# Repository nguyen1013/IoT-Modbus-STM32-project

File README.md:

# IoT-Modbus-STM32-project (this project is a work in progress)

## 1. Introduction
This project showcases a compact but realistic home‑automation system built with STM32 microcontrollers, Modbus RTU over RS‑485, and cloud integration via an IoT gateway. Each STM32 node gathers sensor data—temperature, humidity, light, CO₂, and AC voltage—and sends it to a PC gateway for processing and visualisation. The setup highlights practical embedded engineering: real‑time operation, safe hardware design, reliable communication, and a scalable architecture suitable for smart‑home or educational use.

<p align="center">
  <br>
  <b>The General Project Architecture</b>
</p>

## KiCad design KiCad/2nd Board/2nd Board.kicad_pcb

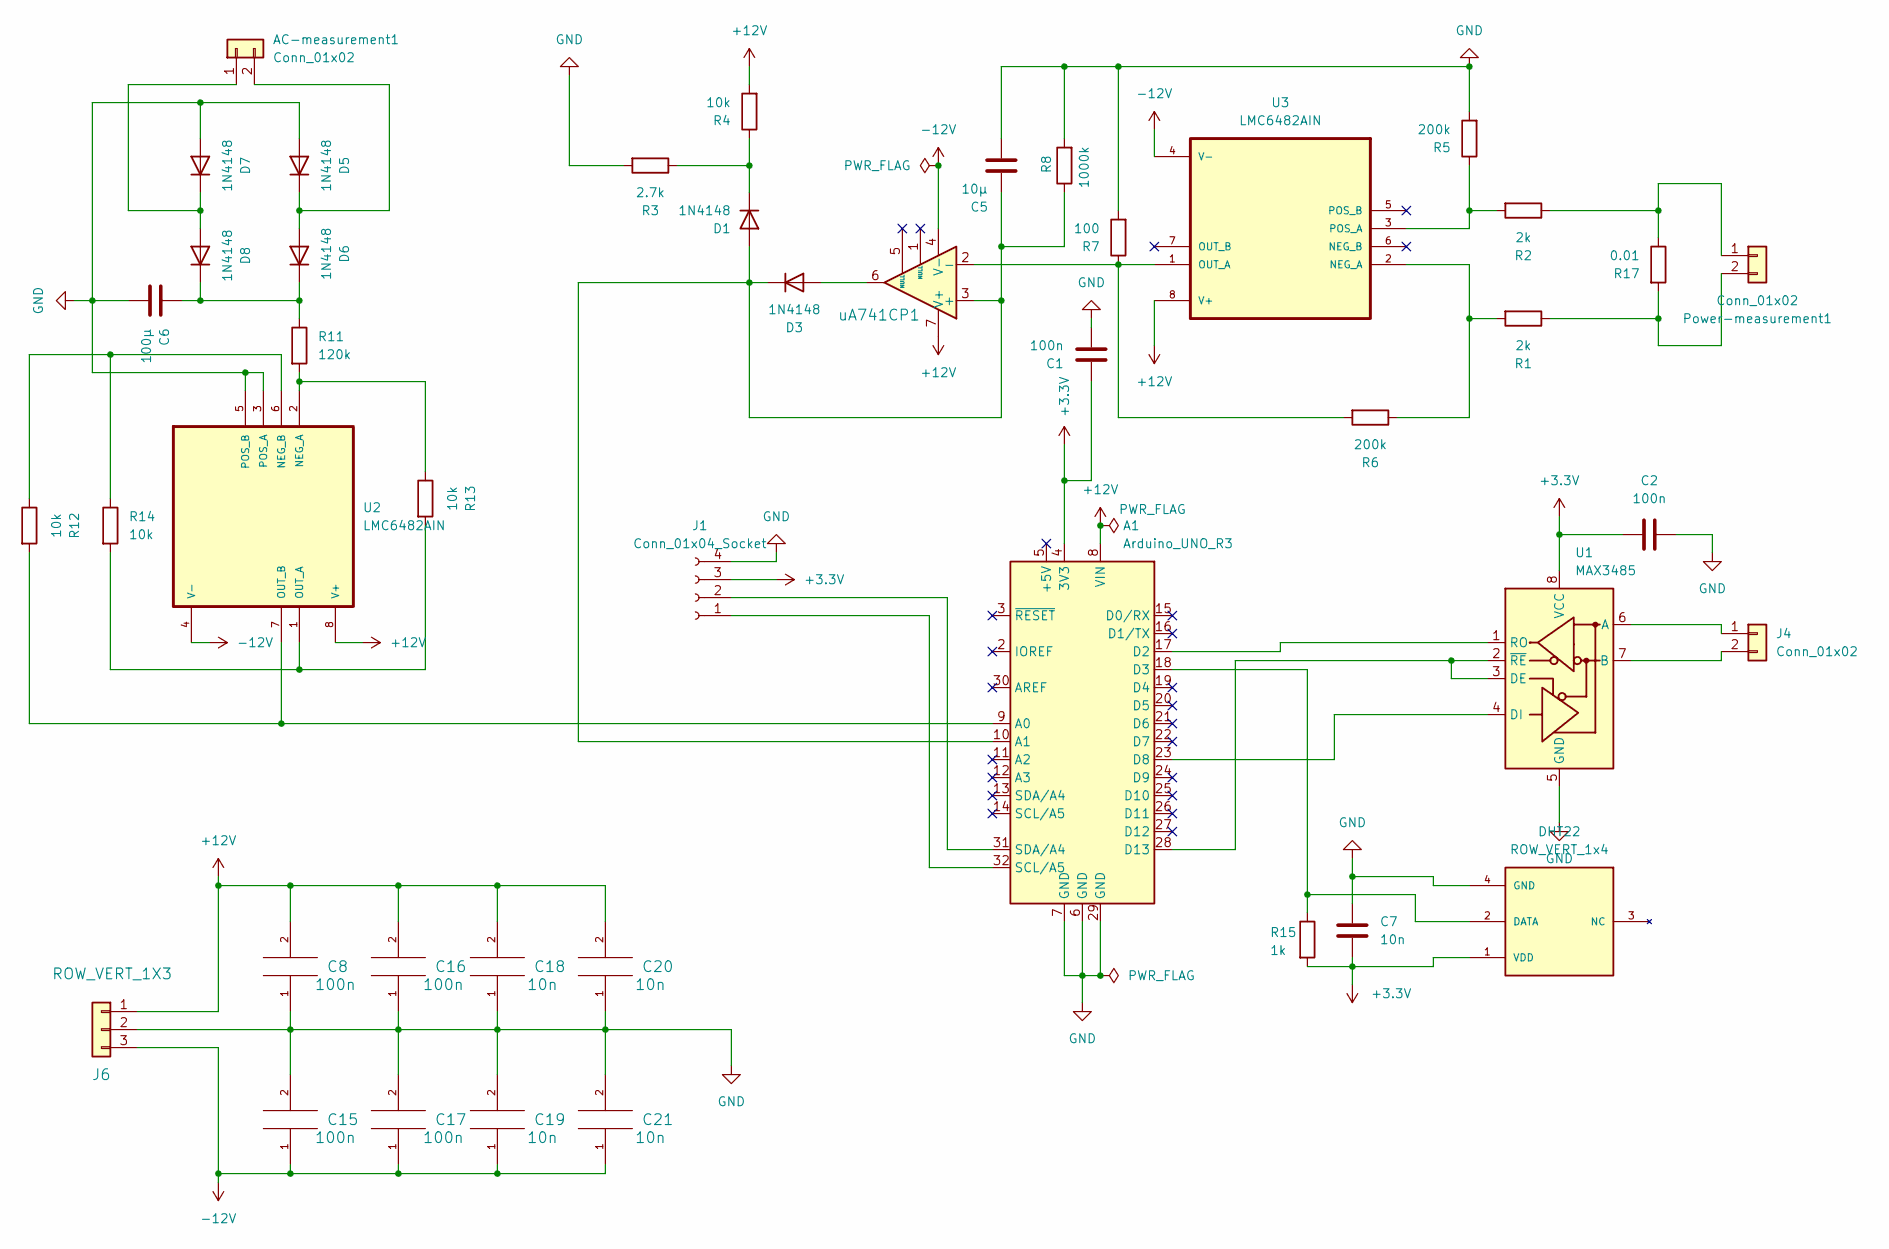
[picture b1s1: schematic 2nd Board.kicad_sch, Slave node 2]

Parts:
A1: Arduino_UNO_R3
AC-measurement1: Conn_01x02; ROW_VERT_1x2
C1, C2: 100n; C_0805_2012Metric
C5: 10μ; C5_0
C6: 100μ; C5_0
C7: 10n; C5_0
C8, C15, C16, C17: 100n; C5_0; Tolerance +-10%
C18, C19, C20, C21: 10n; C5_0; Tolerance +-10%
D1, D3, D5, D6, D7, D8: 1N4148; D_DO-35_SOD27_P7.62mm_Horizontal
DHT22: ROW_VERT_1x4
J1: Conn_01x04_Socket; SOCKET_1x4
J4: Conn_01x02; ROW_VERT_1x2
J6: ROW_VERT_1X3; ROW_VERT_1x3
Power-measurement1: Conn_01x02; ROW_VERT_1x2
R1, R2: 2k; R3_5W
R3: 2.7k; R3_5W
R4, R12, R13, R14: 10k; R3_5W
R5, R6: 200k; R3_5W
R7: 100; R3_5W
R8: 1000k; R3_5W
R11: 120k; R3_5W
R15: 1k; R3_5W
R17: 0.01; R3_5W
U1: MAX3485; DIP-8_W7.62mm
U2, U3: LMC6482AIN; DIP794W45P254L959H508Q8
uA741CP1: uA741CP_DIL8; DIL8

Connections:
+3.3V: A1.4 (3V3), C1.1, C2.1, C7.2, DHT22.1 (VDD), J1.3, R15.2, U1.8 (VCC)
+12V: A1.8 (VIN), C8.2, C16.2, C18.2, C20.2, J6.1, R4.2, U2.8 (V+), U3.8 (V+), uA741CP1.7 (V+)
-12V: C15.1, C17.1, C19.1, C21.1, J6.3, U2.4 (V-), U3.4 (V-), uA741CP1.4 (V-)
GND: A1.6 (GND), A1.7 (GND), A1.29 (GND), C1.2, C2.2, C5.2, C6.2, C7.1, C8.1, C15.2, C16.1, C17.2, C18.1, C19.2, C20.1, C21.2, D5.2 (A), D7.2 (A), DHT22.4 (GND), J1.4, J6.2, R3.2, R5.2, R7.2, R8.2, U1.5 (GND), U2.3 (POS_A), U2.5 (POS_B)
unnamed: A1.9 (A0), R12.2, U2.7 (OUT_B)
unnamed: A1.10 (A1), C5.1, D1.2 (A), D3.1 (K), R8.1, uA741CP1.3 (+)
unnamed: A1.17 (D2), U1.1 (RO)
unnamed: A1.18 (D3), DHT22.2 (DATA), R15.1
unnamed: A1.23 (D8), U1.4 (DI)
unnamed: A1.28 (D13), U1.2 (~RE), U1.3 (DE)
unnamed: AC-measurement1.1, D7.1 (K), D8.2 (A)
unnamed: AC-measurement1.2, D5.1 (K), D6.2 (A)
unnamed: D1.1 (K), R3.1, R4.1
unnamed: D3.2 (A), uA741CP1.6
unnamed: C6.1, D6.1 (K), D8.1 (K), R11.1
unnamed: A1.32 (SCL/A5), J1.1
unnamed: A1.31 (SDA/A4), J1.2
unnamed: J4.1, U1.6 (A)
unnamed: J4.2, U1.7 (B)
unnamed: Power-measurement1.1, R2.1, R17.1
unnamed: Power-measurement1.2, R1.1, R17.2
unnamed: R11.2, R13.1, U2.2 (NEG_A)
unnamed: R12.1, R14.1, U2.6 (NEG_B)
unnamed: R13.2, R14.2, U2.1 (OUT_A)
unnamed: R1.2, R6.1, U3.2 (NEG_A)
unnamed: R6.2, R7.1, U3.1 (OUT_A), uA741CP1.2 (-)
unnamed: R2.2, R5.1, U3.3 (POS_A)

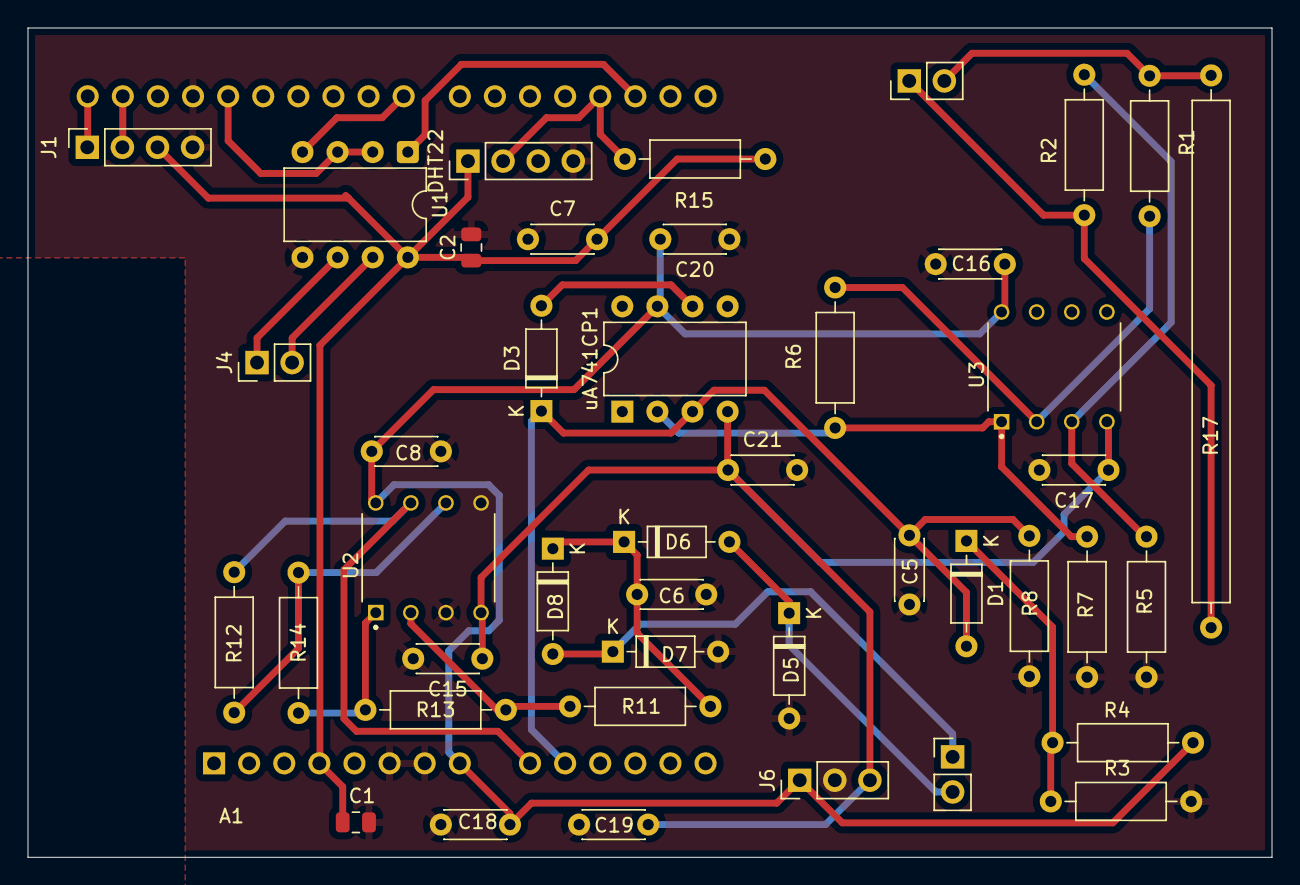
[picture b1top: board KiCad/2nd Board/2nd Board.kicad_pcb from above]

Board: 2 copper layers, 90.0 x 60.0 mm, 44 parts (1 on the bottom side), 27 nets.

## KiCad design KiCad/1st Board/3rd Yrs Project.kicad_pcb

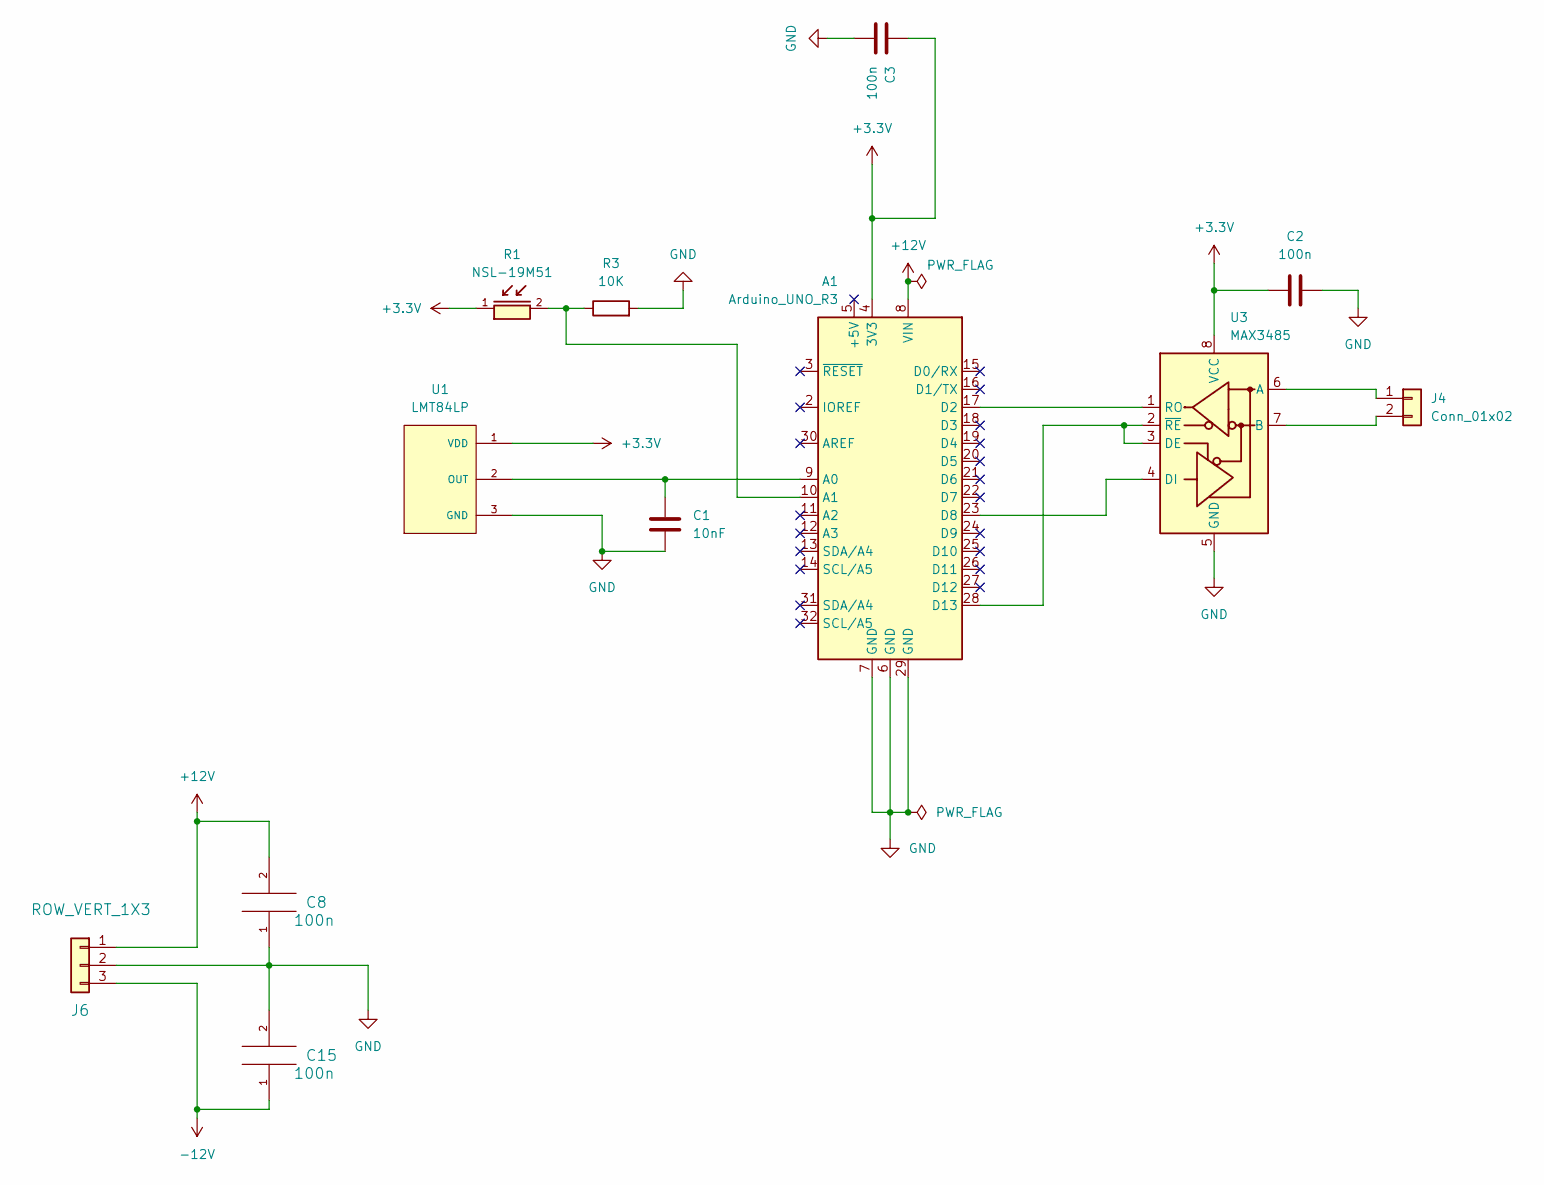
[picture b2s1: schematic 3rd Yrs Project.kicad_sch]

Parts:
A1: Arduino_UNO_R3
C1: 10nF; C5_0
C2, C3: 100n; C5_0
C8, C15: 100n; C5_0; Tolerance +-10%
J4: Conn_01x02; ROW_VERT_1x2
J6: ROW_VERT_1X3; ROW_VERT_1x3
R1: NSL-19M51; ROW_VERT_1x2
R3: 10K; R3_5W
U1: LMT84LP; ROW_VERT_1x3; PARTREV 4215214/B
U3: MAX3485; DIP762W47P254L991H457Q8

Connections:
+3.3V: A1.4 (3V3), C2.1, C3.1, R1.1, U1.1 (VDD), U3.8 (VCC)
+12V: A1.8 (VIN), C8.2, J6.1
-12V: C15.1, J6.3
GND: A1.6 (GND), A1.7 (GND), A1.29 (GND), C1.1, C2.2, C3.2, C8.1, C15.2, J6.2, R3.2, U1.3 (GND), U3.5 (GND)
unnamed: A1.9 (A0), C1.2, U1.2 (OUT)
unnamed: A1.10 (A1), R1.2, R3.1
unnamed: A1.17 (D2), U3.1 (RO)
unnamed: A1.23 (D8), U3.4 (DI)
unnamed: A1.28 (D13), U3.2 (~RE), U3.3 (DE)
unnamed: J4.1, U3.6 (A)
unnamed: J4.2, U3.7 (B)

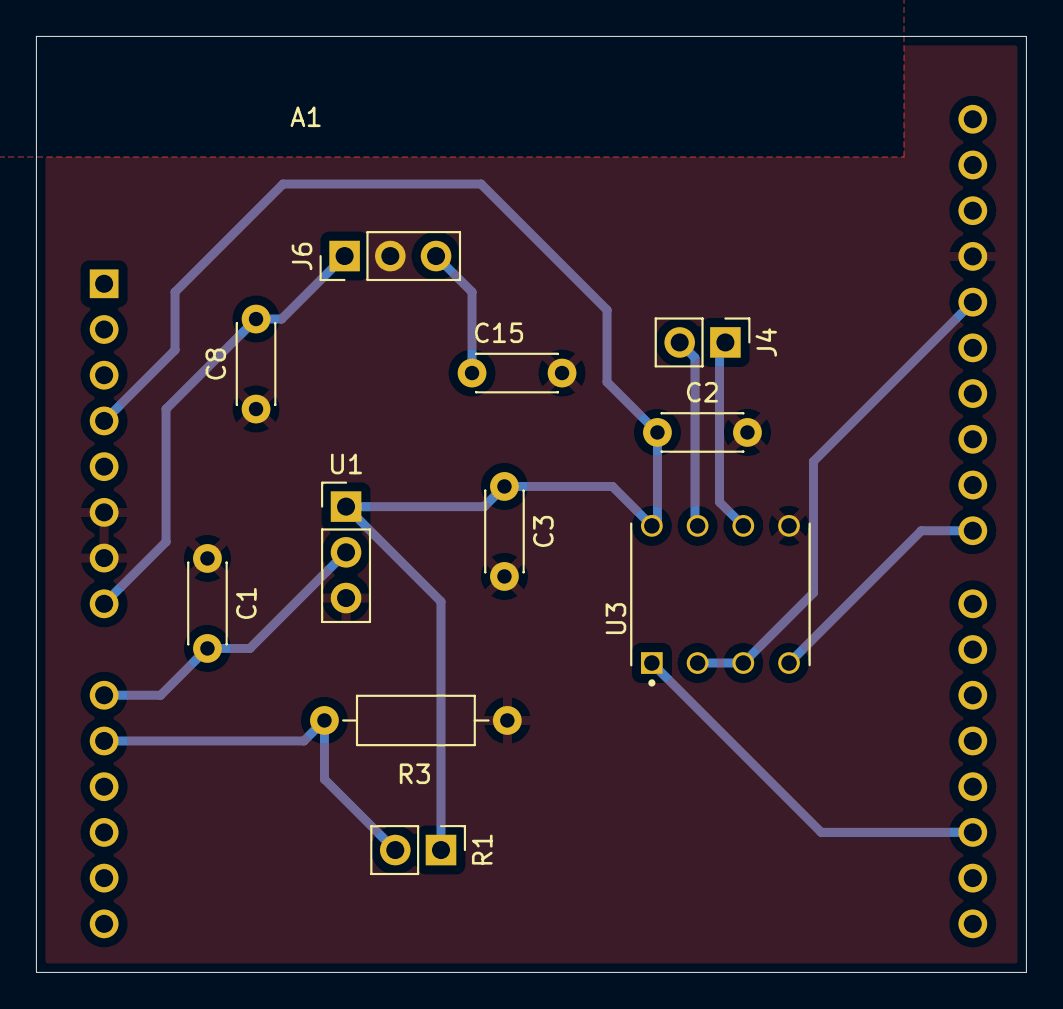
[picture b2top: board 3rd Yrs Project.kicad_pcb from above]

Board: 2 copper layers, 55.0 x 52.0 mm, 12 parts (0 on the bottom side), 11 nets.

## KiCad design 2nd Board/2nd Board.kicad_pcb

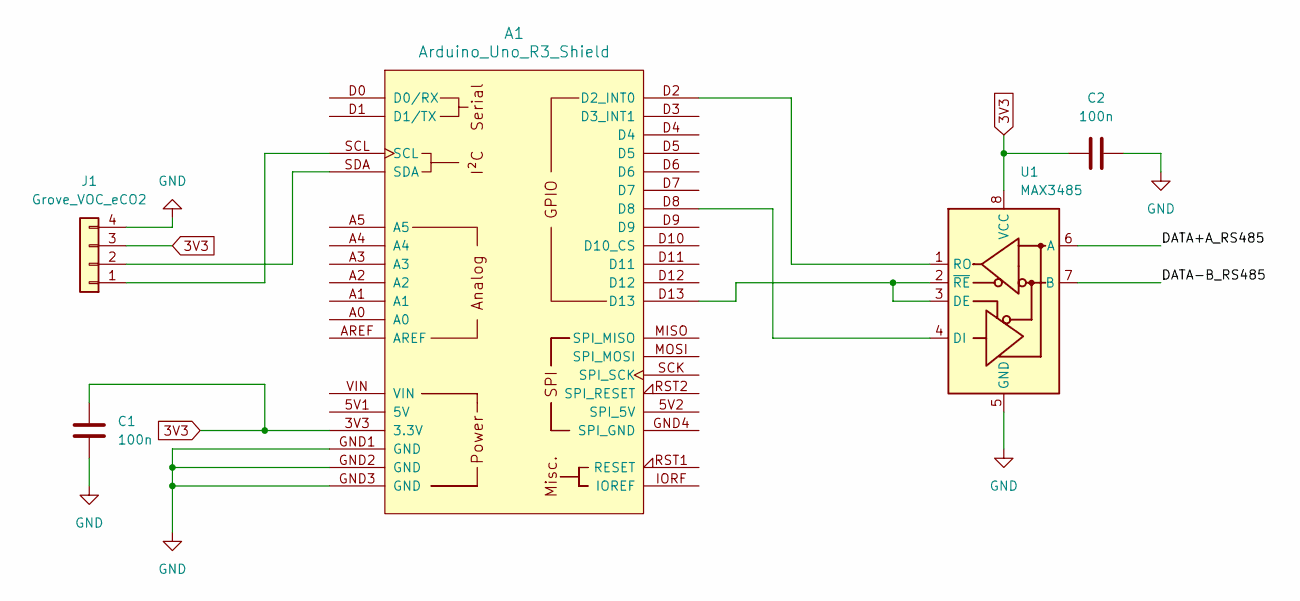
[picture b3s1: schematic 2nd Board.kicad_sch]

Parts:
A1: Arduino_Uno_R3_Shield
C1, C2: 100n; C_0805_2012Metric
J1: Grove_VOC_eCO2; PinHeader_1x04_P2.54mm_Vertical
U1: MAX3485; SOIC-8_3.9x4.9mm_P1.27mm

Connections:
3V3: A1.3V3 (3.3V), C1.1, C2.1, J1.3 (3V3), U1.8 (VCC)
/DATA+A_RS485: U1.6 (A)
/DATA-B_RS485: U1.7 (B)
GND: A1.GND1 (GND), A1.GND2 (GND), A1.GND3 (GND), C1.2, C2.2, J1.4 (GND), U1.5 (GND)
unnamed: A1.D2 (D2_INT0), U1.1 (RO)
unnamed: A1.SCL, J1.1 (SCL)
unnamed: A1.SDA, J1.2 (SDA)
unnamed: A1.D13, U1.2 (~RE), U1.3 (DE)
unnamed: A1.D8, U1.4 (DI)

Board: 2 copper layers, 5 parts (0 on the bottom side), 7 nets, no tracks yet.

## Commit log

2026-01-16 add gitginore file
2026-01-16 create datasheet folder and files
2026-01-16 driver for lmt84p and nsl-19-m51
2026-01-25 remove basic drivers
2026-01-25 update new driver lmt84lp
2026-01-25 update new driver nsl-19m51
2026-01-25 driver dht-22
2026-01-25 driver grove sgp30
2026-01-26 Kicad Project
2026-01-27 2bd PCB
2026-01-27 1st PCB
2026-01-31 combine sensor lmt84lp and nsl19m51 and tested with modbus
2026-01-31 update program for modbus-master
2026-01-31 revies response frame length to 9
2026-02-01 refactor lmt84lp driver
2026-02-01 refactor nsl-19m51 sensor
2026-02-01 Initialize README
    Added project introduction and overview.
2026-02-01 Update project architechture image
2026-02-04 1st Board Updated w/o OPAMP
2026-02-15 update dht22 and grove sgp30, handling failed reading slave
2026-02-17 Update reading dht22 and sgp30
2026-02-17 slave node 2: reading dht22 and sgp30
2026-02-28 new driver for slave node 2 (dht22, sgp30, measuring ac voltage and power consumption)
2026-02-28 update new driver for modbus slave node 1 (lmt84p, nsl19m51)
2026-02-28 LT Spice for AC and power consumption measurement
2026-02-28 update modbus master including ac measurement and power consumption
2026-02-28 update modbus-slave-node-2
2026-03-02 1st Board UPDATED!
2026-03-02 2nd Board UPDATED!
2026-03-03 2nd Board Updated
2026-03-09 Fixed The Arduino Footprint
    The Footprint weren't accurate to be place on STM32 so I fixed it.
2026-03-09 Fixed The Arduino Footprint and Redesign PCB
2026-03-09 Redesigned The Whole PCB
2026-03-09 Redesign Whole PCB
2026-03-09 Redesigned PCB
2026-03-09 Fixed PCB
2026-03-15 PCB fixed (Put trace at the back side)
2026-03-18 upload the project report
2026-03-18 update LTspice
2026-03-19 Create temp
2026-03-19 PCB Final
2026-03-19 2nd Board Final
2026-03-19 1st Board Final
2026-03-19 Create tmp
2026-03-19 Create www
2026-03-20 update validation for nsl19m51
2026-03-23 update project report
